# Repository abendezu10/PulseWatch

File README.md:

# PulseWatch
A Smart Watch that uses the STM32L4

## Schematic

## Printed Circuit Board (PCB)

## 3D Model

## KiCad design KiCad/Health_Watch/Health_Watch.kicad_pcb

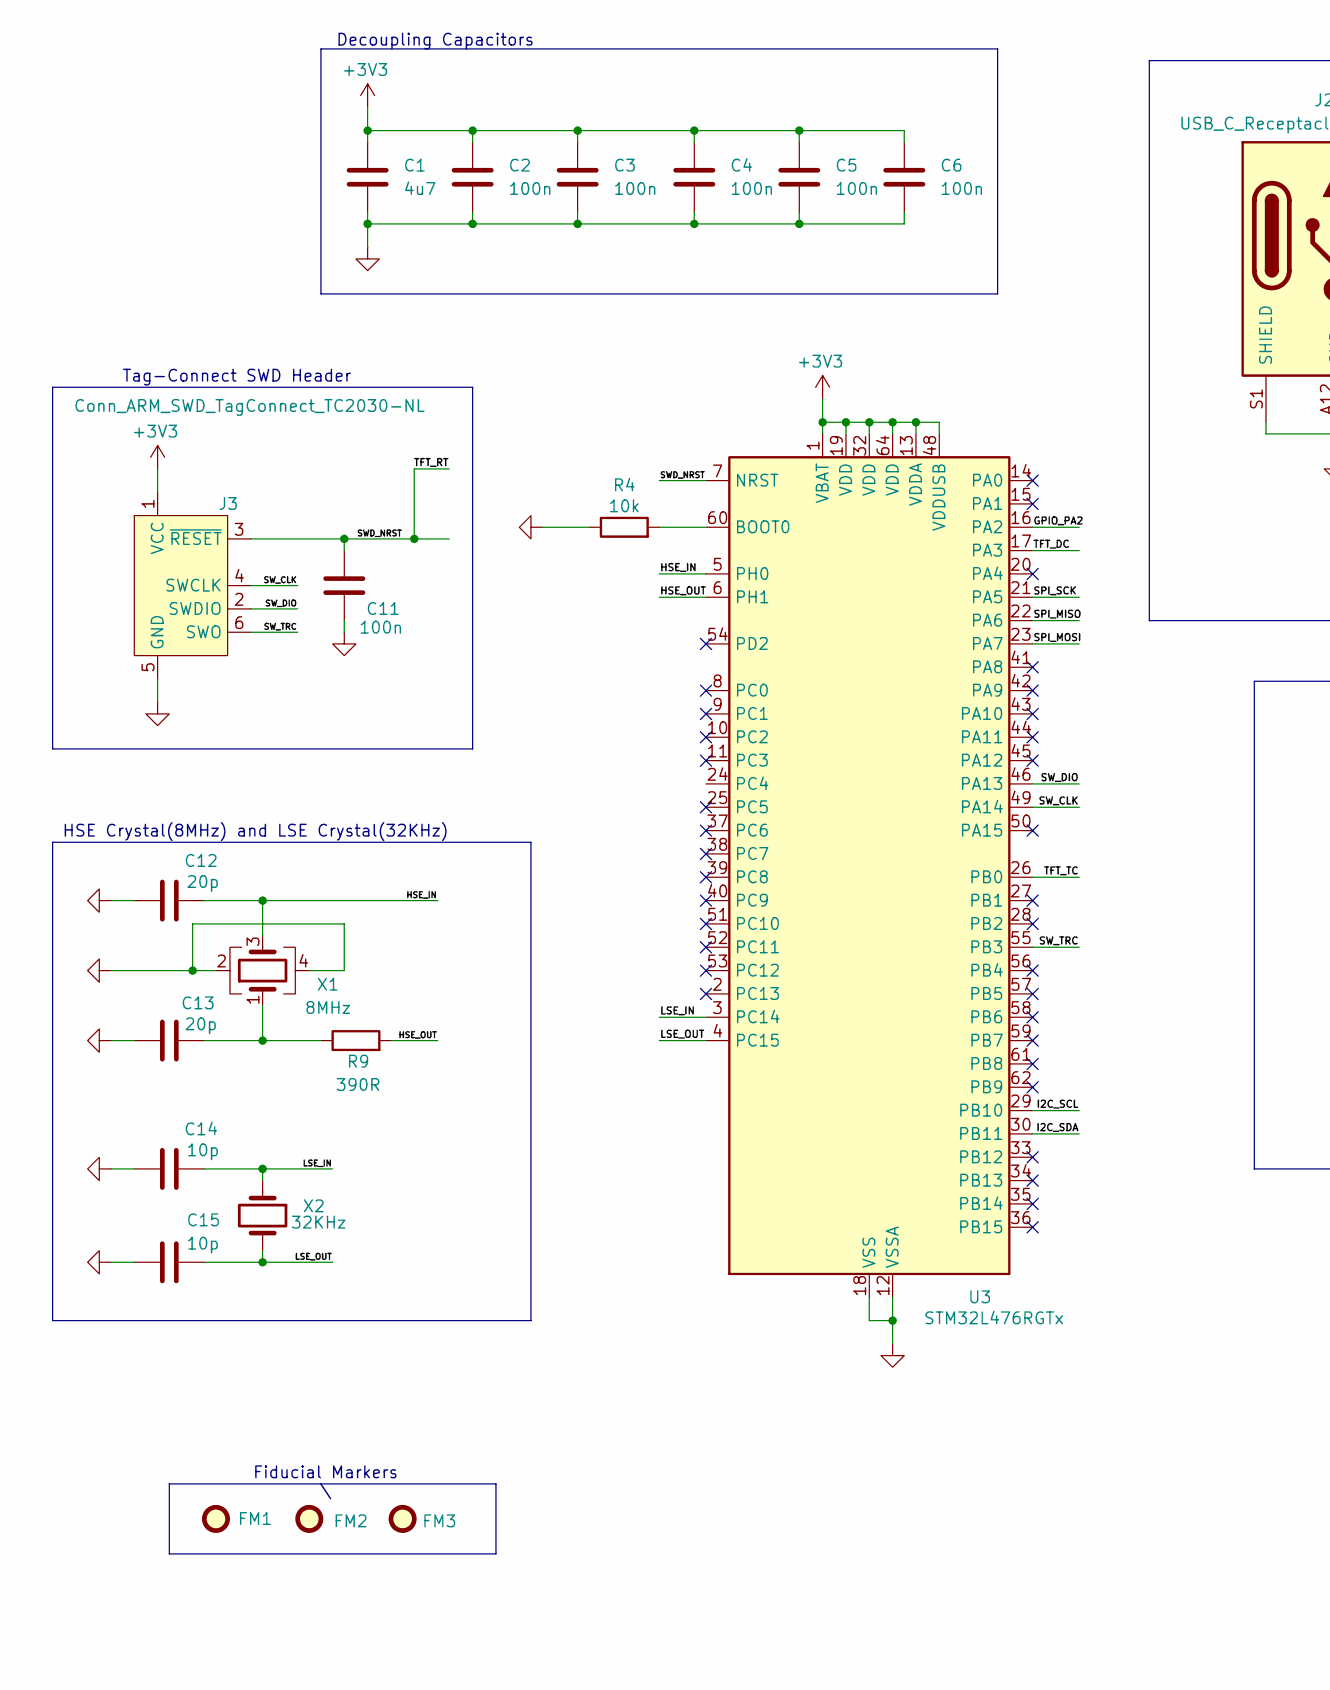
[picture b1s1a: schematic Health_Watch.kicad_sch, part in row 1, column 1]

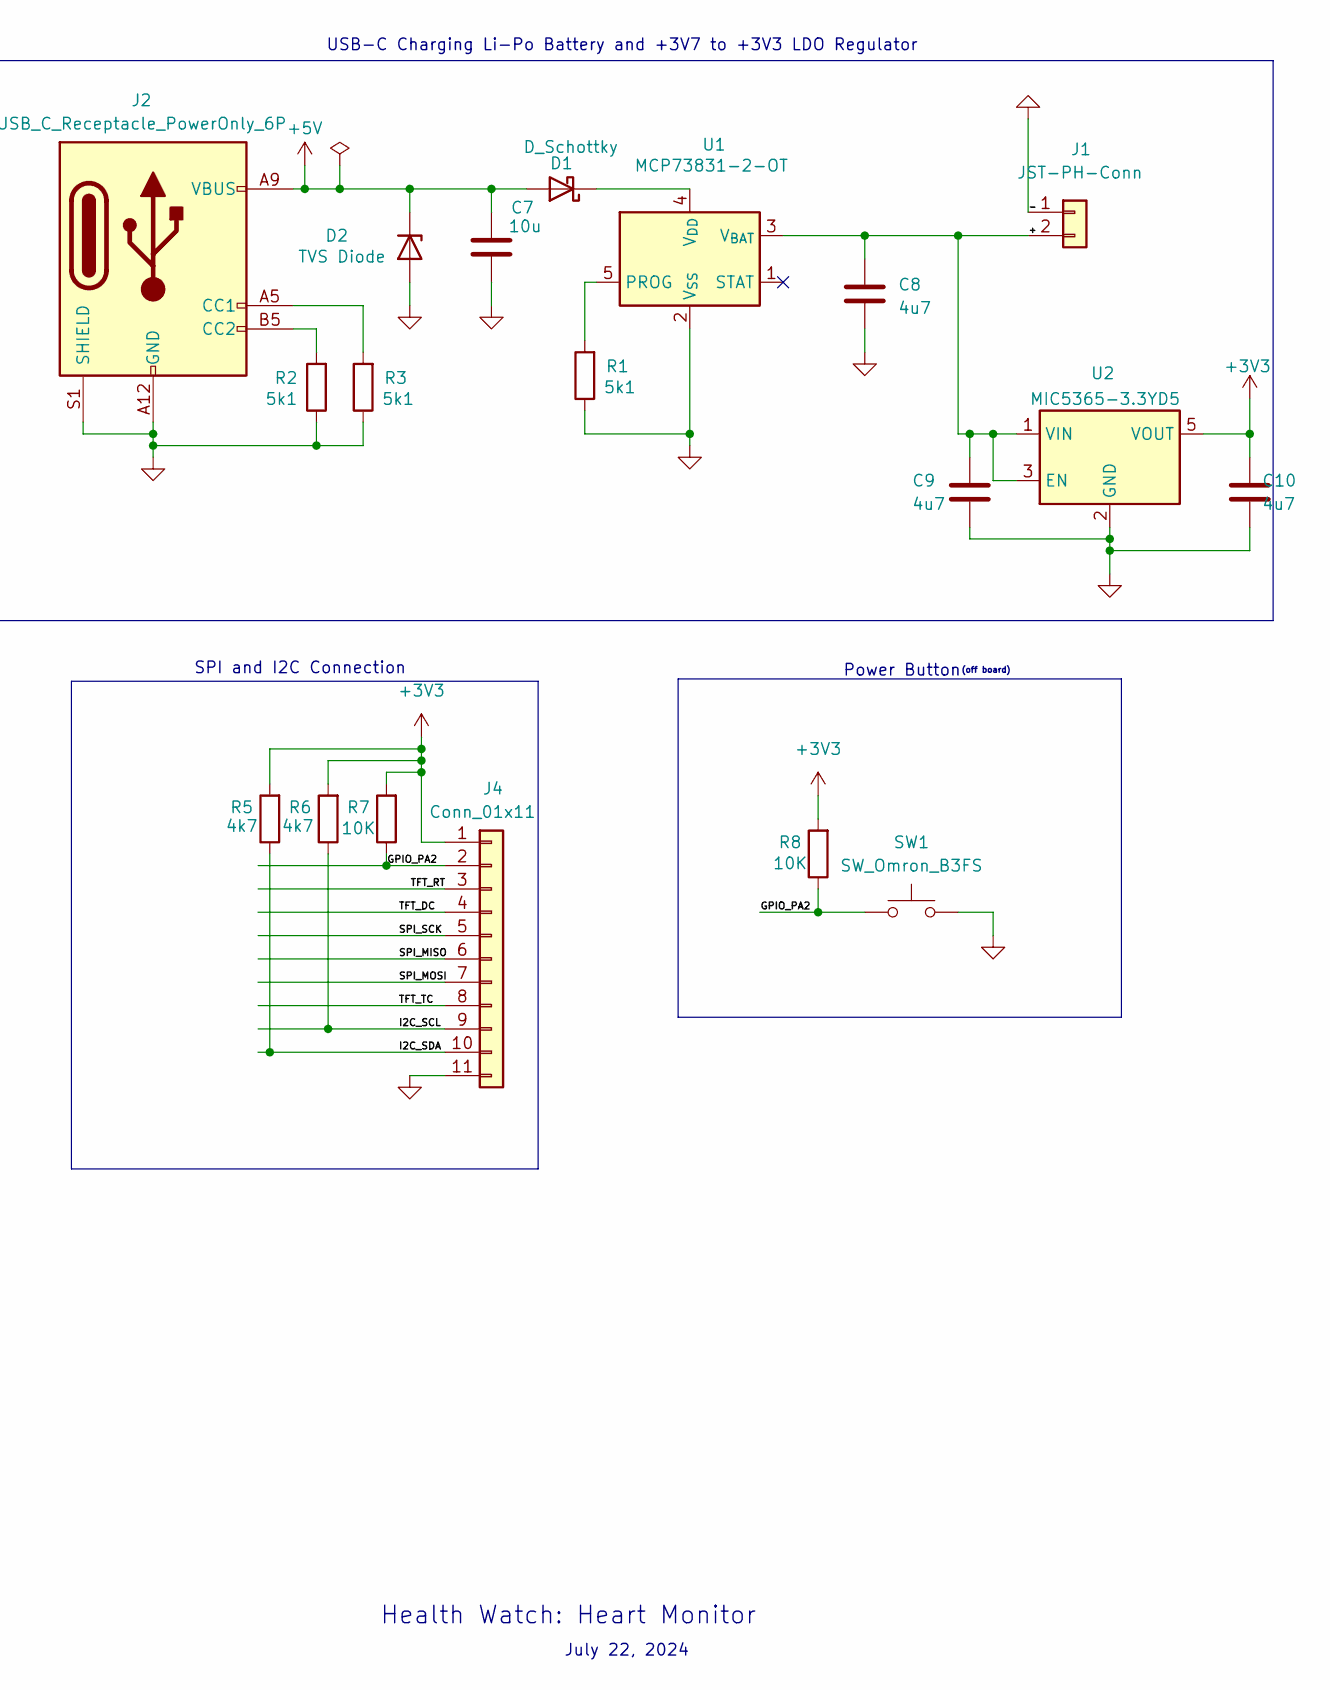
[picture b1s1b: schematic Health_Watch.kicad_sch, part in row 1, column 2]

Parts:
C1, C8, C9, C10: 4u7; C_0603_1608Metric; Manufacturer Part Number LMK107BJ475KA-T
C2, C3, C4, C5, C6, C11: 100n; C_0402_1005Metric; Manufacturer Part Number 0402X7R104KT7AT
C7: 10u; C_0805_2012Metric; Manufacturer Part Number TMK212BBJ106KG8T
C12, C13: 20p; C_0402_1005Metric; Manufacturer Part Number C0402C200F5GACTU
C14, C15: 10p; C_0402_1005Metric; Manufacturer Part Number MBASU105SCH100JFNA01
D1: D_Schottky; D_SOD-523; Manufacturer Part Number ZHCS350TA
D2: TVS Diode; D_SOD-923; Manufacturer Part Number ESD9B5.0ST5G
FM1, FM2, FM3: Fiducial; Fiducial_0.75mm_Mask1.5mm
J1: JST-PH-Conn; CONN_S2B-PH-K-S_JST; Manufacturer Part Number S2B-PH-K-S
J2: USB_C_Receptacle_PowerOnly_6P; USB_C_Receptacle_GCT_USB4125-xx-x_6P_TopMnt_Horizontal; Manufacturer Part Number USB4125-GF-A
J3: Conn_ARM_SWD_TagConnect_TC2030-NL; Tag-Connect_TC2030-IDC-NL_2x03_P1.27mm_Vertical
J4: Conn_01x11; 01x10_Conn_Hole
R1, R2, R3: 5k1; R_0402_1005Metric; Manufacturer Part Number MCS04020C5101FE000
R4: 10k; R_0603_1608Metric; Manufacturer Part Number CRCW060310K0FKEA
R5, R6: 4k7; R_0402_1005Metric; Manufacturer Part Number CRCW04024K70FKEDC
R7: 10K; R_0603_1608Metric; Manufacturer Part Number CRCW060310K0FKEA
R8: 10K; R_0603_1608Metric
R9: 390R; R_0603_1608Metric; Manufacturer Part Number ERJ-PA3F3900V
SW1: SW_Omron_B3FS; SW_TH_Tactile_Omron_B3F-10xx
U1: MCP73831-2-OT; SOT-23-5; Manufacturer Part Number MCP73831T-2ACI/OT
U2: MIC5365-3.3YD5; SOT-23-5; Manufacturer Part Number MIC5365-3.3YD5-TR
U3: STM32L476RGTx; LQFP-64_10x10mm_P0.5mm; Manufacturer Part Number STM32L476RGT6
X1: 8MHz; Crystal_SMD_3225-4Pin_3.2x2.5mm; Manufacturer Part Number ECS-2016MV-080-DN-TR
X2: 32KHz; Crystal_SMD_EuroQuartz_EQ161-2Pin_3.2x1.5mm; Manufacturer Part Number FC-135R 32.7680KA-A3

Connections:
+3V3: C1.1, C2.1, C3.1, C4.1, C5.1, C6.1, C10.1, J3.1 (VCC), J4.1, R5.2, R6.2, R7.2, R8.2, U2.5 (VOUT), U3.1 (VBAT), U3.13 (VDDA), U3.19 (VDD), U3.32 (VDD), U3.48 (VDDUSB), U3.64 (VDD)
+5V: C7.1, D1.2 (A), D2.1 (K), J2.A9 (VBUS), J2.B9 (VBUS)
/+: C8.1, C9.1, J1.2, U1.3 (V_{BAT}), U2.1 (VIN), U2.3 (EN)
/GPIO_PA2: J4.2, R7.1, R8.1, SW1.1, U3.16 (PA2)
/HSE_IN: C12.1, U3.5 (PH0), X1.3
/HSE_OUT: R9.2, U3.6 (PH1)
/I2C_SCL: J4.9, R6.1, U3.29 (PB10)
/I2C_SDA: J4.10, R5.1, U3.30 (PB11)
/LSE_IN: C14.1, U3.3 (PC14), X2.1
/LSE_OUT: C15.1, U3.4 (PC15), X2.2
/SPI_MISO: J4.6, U3.22 (PA6)
/SPI_MOSI: J4.7, U3.23 (PA7)
/SPI_SCK: J4.5, U3.21 (PA5)
/SWD_NRST: C11.1, J3.3 (~RESET), J4.3, U3.7 (NRST)
/SW_CLK: J3.4 (SWCLK), U3.49 (PA14)
/SW_DIO: J3.2 (SWDIO), U3.46 (PA13)
/SW_TRC: J3.6 (SWO), U3.55 (PB3)
/TFT_DC: J4.4, U3.17 (PA3)
/TFT_TC: J4.8, U3.26 (PB0)
GND: C1.2, C2.2, C3.2, C4.2, C5.2, C6.2, C7.2, C8.2, C9.2, C10.2, C11.2, C12.2, C13.1, C14.2, C15.2, D2.2 (A), J1.1, J2.A12 (GND), J2.B12 (GND), J2.S1 (SHIELD), J3.5 (GND), J4.11, R1.1, R2.1, R3.1, R4.1, SW1.2, U1.2 (V_{SS}), U2.2 (GND), U3.12 (VSSA), U3.18 (VSS), U3.31 (VSS), U3.47 (VSS), U3.63 (VSS), X1.2, X1.4
unnamed: C13.2, R9.1, X1.1
unnamed: D1.1 (K), U1.4 (V_{DD})
unnamed: J2.A5 (CC1), R3.2
unnamed: J2.B5 (CC2), R2.2
unnamed: R1.2, U1.5 (PROG)
unnamed: R4.2, U3.60 (BOOT0)

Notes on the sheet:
Decoupling Capacitors
(off board)
Health Watch: Heart Monitor
Tag-Connect SWD Header
USB-C Charging Li-Po Battery and +3V7 to +3V3 LDO Regulator
Power Button
SPI and I2C Connection
HSE Crystal(8MHz) and LSE Crystal(32KHz)
July 22, 2024
Fiducial Markers \

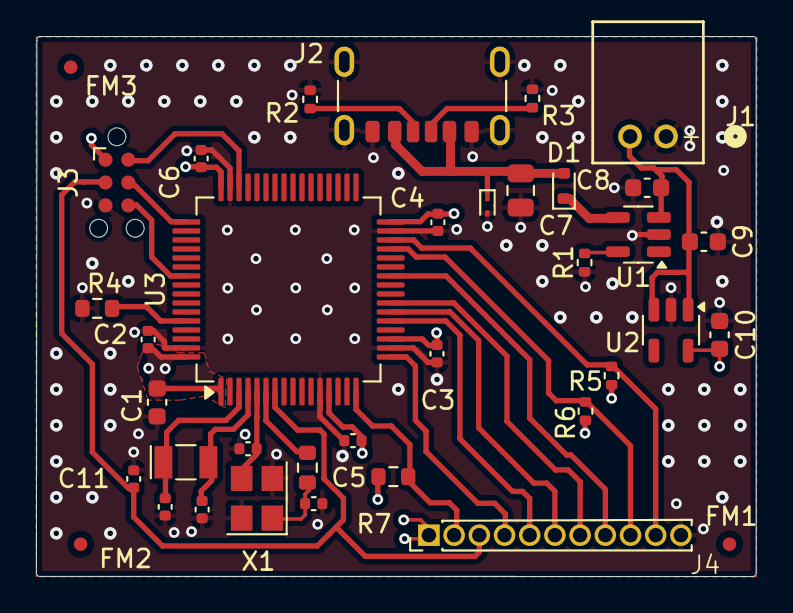
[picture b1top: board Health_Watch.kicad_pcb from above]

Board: 4 copper layers, 40.0 x 30.0 mm, 37 parts (0 on the bottom side), 26 nets.

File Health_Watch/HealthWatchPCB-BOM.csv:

"Reference","Value","Footprint","Distrubutor Link","Manufacturer","Manufacturer Part Number"
"J4","Conn_01x11","Connector_PinHeader_1.00mm:01x10_Conn_Hole","","",""
"SW1","SW_Omron_B3FS","Button_Switch_THT:SW_TH_Tactile_Omron_B3F-10xx","","",""
"J1","JST-PH-Conn","Health_Watch:CONN_S2B-PH-K-S_JST","https://www.digikey.com/en/products/detail/jst-sales-america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"," JST Sales America Inc."," S2B-PH-K-S"
"U1","MCP73831-2-OT","Package_TO_SOT_SMD:SOT-23-5","https://www.mouser.com/ProductDetail/Microchip-Technology/MC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","Microchip Technology"," MCP73831T-2ACI/OT"
"D1","D_Schottky","Diode_SMD:D_SOD-523","https://www.mouser.com/ProductDetail/Diodes-Incorporated/ZHC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","Diodes Incorporated"," ZHCS350TA"
"C2","100n","Capacitor_SMD:C_0402_1005Metric","https://www.mouser.com/ProductDetail/KYOCERA-AVX/0402X7R104K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","KYOCERA AVX","0402X7R104KT7AT"
"C3","100n","Capacitor_SMD:C_0402_1005Metric","https://www.mouser.com/ProductDetail/KYOCERA-AVX/0402X7R104K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","KYOCERA AVX","0402X7R104KT7AT"
"C4","100n","Capacitor_SMD:C_0402_1005Metric","https://www.mouser.com/ProductDetail/KYOCERA-AVX/0402X7R104K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","KYOCERA AVX","0402X7R104KT7AT"
"C5","100n","Capacitor_SMD:C_0402_1005Metric","https://www.mouser.com/ProductDetail/KYOCERA-AVX/0402X7R104K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","KYOCERA AVX","0402X7R104KT7AT"
"C6","100n","Capacitor_SMD:C_0402_1005Metric","https://www.mouser.com/ProductDetail/KYOCERA-AVX/0402X7R104K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","KYOCERA AVX","0402X7R104KT7AT"
"C11","100n","Capacitor_SMD:C_0402_1005Metric","https://www.mouser.com/ProductDetail/KYOCERA-AVX/0402X7R104K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","KYOCERA AVX","0402X7R104KT7AT"
"C12","20p","Capacitor_SMD:C_0402_1005Metric","https://www.mouser.com/ProductDetail/KEMET/C0402C200F5GACTU?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","KEMET","C0402C200F5GACTU"
"C13","20p","Capacitor_SMD:C_0402_1005Metric","https://www.mouser.com/ProductDetail/KEMET/C0402C200F5GACTU?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","KEMET","C0402C200F5GACTU"
"R5","4k7","Resistor_SMD:R_0402_1005Metric","https://www.mouser.com/ProductDetail/Vishay-Dale/CRCW04024K7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","Vishay / Dale","CRCW04024K70FKEDC"
"R6","4k7","Resistor_SMD:R_0402_1005Metric","https://www.mouser.com/ProductDetail/Vishay-Dale/CRCW04024K7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","Vishay / Dale","CRCW04024K70FKEDC"
"R4","10k","Resistor_SMD:R_0603_1608Metric","https://www.mouser.com/ProductDetail/Vishay-Dale/CRCW060310K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","Vishay / Dale","CRCW060310K0FKEI"
"R7","10K","Resistor_SMD:R_0603_1608Metric","https://www.mouser.com/ProductDetail/Vishay-Dale/CRCW060310K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","Vishay / Dale","CRCW060310K0FKEI"
"X1","8MHz","Crystal:Crystal_SMD_3225-4Pin_3.2x2.5mm","https://www.mouser.com/ProductDetail/ECS/ECS-2016MV-080-DN-T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","ECS","ECS-2016MV-080-DN-TR"
"R9","390R","Resistor_SMD:R_0603_1608Metric","https://www.mouser.com/ProductDetail/Panasonic/ERJ-PA3F3900V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","Panasonic","ERJ-PA3F3900V"
"D2","TVS Diode","Diode_SMD:D_SOD-923","https://www.mouser.com/ProductDetail/onsemi/ESD9B5.0ST5G?qs=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","onsemi","ESD9B5.0ST5G"
"X2","32KHz","Crystal:Crystal_SMD_EuroQuartz_EQ161-2Pin_3.2x1.5mm","https://www.mouser.com/ProductDetail/Epson-Timing/FC-135R-32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","Epson Timing","FC-135R 32.7680KA-A3"
"C1","4u7","Capacitor_SMD:C_0603_1608Metric","https://www.mouser.com/ProductDetail/TAIYO-YUDEN/LMK107BJ475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","TAIYO YUDEN","LMK107BJ475KA-T"
"C8","4u7","Capacitor_SMD:C_0603_1608Metric","https://www.mouser.com/ProductDetail/TAIYO-YUDEN/LMK107BJ475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","TAIYO YUDEN","LMK107BJ475KA-T"
"C9","4u7","Capacitor_SMD:C_0603_1608Metric","https://www.mouser.com/ProductDetail/TAIYO-YUDEN/LMK107BJ475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","TAIYO YUDEN","LMK107BJ475KA-T"
"C10","4u7","Capacitor_SMD:C_0603_1608Metric","https://www.mouser.com/ProductDetail/TAIYO-YUDEN/LMK107BJ475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","TAIYO YUDEN","LMK107BJ475KA-T"
"C14","10p","Capacitor_SMD:C_0402_1005Metric","https://www.mouser.com/ProductDetail/TAIYO-YUDEN/MBASU105SCH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","TAIYO YUDEN","MBASU105SCH100JFNA01"
"C15","10p","Capacitor_SMD:C_0402_1005Metric","https://www.mouser.com/ProductDetail/TAIYO-YUDEN/MBASU105SCH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","TAIYO YUDEN","MBASU105SCH100JFNA01"
"R1","5k1","Resistor_SMD:R_0402_1005Metric","https://www.mouser.com/ProductDetail/Vishay-Beyschlag/MCS040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","Vishay / Beyschlag","MCS04020C5101FE000"
"R2","5k1","Resistor_SMD:R_0402_1005Metric","https://www.mouser.com/ProductDetail/Vishay-Beyschlag/MCS040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","Vishay / Beyschlag","MCS04020C5101FE000"
"R3","5k1","Resistor_SMD:R_0402_1005Metric","https://www.mouser.com/ProductDetail/Vishay-Beyschlag/MCS040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","Vishay / Beyschlag","MCS04020C5101FE000"
"U2","MIC5365-3.3YD5","Package_TO_SOT_SMD:SOT-23-5","https://www.mouser.com/ProductDetail/Microchip-Technology/MI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","Microchip Technology","MIC5365-3.3YD5-TR"
"U3","STM32L476RGTx","Package_QFP:LQFP-64_10x10mm_P0.5mm","https://www.mouser.com/ProductDetail/STMicroelectronics/STM3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","STMicroelectronics","STM32L476RGT6"
"C7","10u","Capacitor_SMD:C_0805_2012Metric","https://www.mouser.com/ProductDetail/TAIYO-YUDEN/TMK212BBJ10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","TAIYO YUDEN","TMK212BBJ106KG8T"
"J2","USB_C_Receptacle_PowerOnly_6P","Connector_USB:USB_C_Receptacle_GCT_USB4125-xx-x_6P_TopMnt_Horizontal","https://www.mouser.com/ProductDetail/GCT/USB4125-GF-A?qs=KUo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","GCT","USB4125-GF-A"

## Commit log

2024-07-22 adding KiCad Project
2024-07-22 Add .DS_Store to .gitignore and remove from index
2024-07-23 Updated Schematic KiCad
2024-09-21 adding schematic and PCB layout
2024-09-22 added stm32 project
2024-10-21 putting up to date:
2024-10-21 update corrupted .project file
2024-10-21 added new stm32 project
